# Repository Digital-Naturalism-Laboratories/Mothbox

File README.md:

# Mothbox
Developing an open source,low cost automated system for Moth-Lighting photography 

look at the wiki for up to date information on assembly and usage
https://github.com/Digital-Naturalism-Laboratories/Mothbox/wiki

It's a compact, low cost device you can get running with simple modifications of off-the-shelf parts! And no soldering really needed!

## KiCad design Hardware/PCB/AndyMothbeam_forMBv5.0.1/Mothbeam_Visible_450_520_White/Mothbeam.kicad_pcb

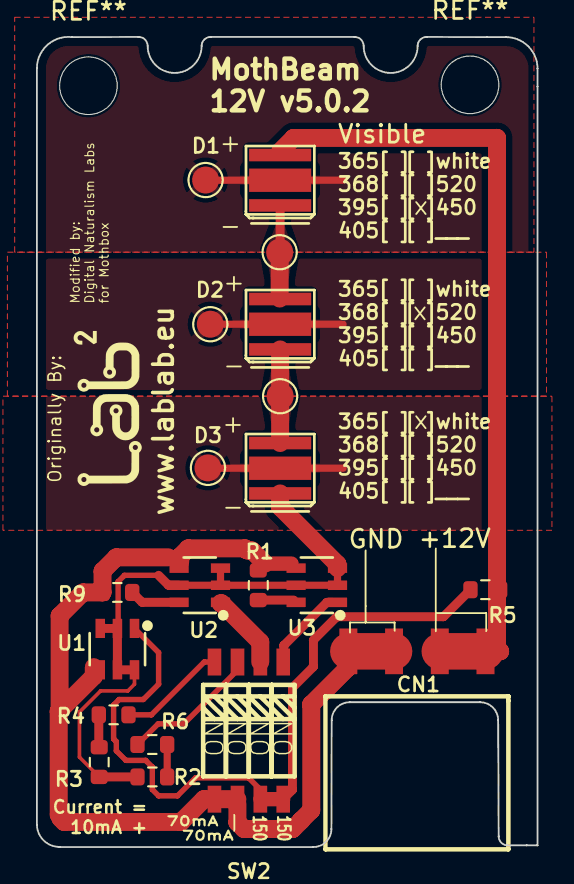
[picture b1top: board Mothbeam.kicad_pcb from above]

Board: 2 copper layers, 27.8 x 45.0 mm, 21 parts (0 on the bottom side), 17 nets.

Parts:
CN1: X6511FRS-04-C85D30; HDR-SMD_4P-P2.54-H-F
D1: LED1; LED-SMD_3P-L3.5-W3.5-R-RD-C
D2: LED2; LED-SMD_3P-L3.5-W3.5-R-RD-C
D3: LED3; LED-SMD_3P-L3.5-W3.5-R-RD-C
H1: LabLab Logo; logo_10mm_5mm
R1, R2, R3, R4, R5, R6, R9: 5.1 1/3 W; R_0603_1608Metric
SW2: SW_DIP_x04; SW-SMD_8P-L6.7-W5.4-P1.27-LS8.5
TP1, TP2, TP3, TP4, TP5: LED2+; TestPoint_Pad_D1.5mm
U1, U2, U3: BCR421U; SOT-23-6_L2.9-W1.6-P0.95-LS2.8-BL

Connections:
/LED+: CN1.3, CN1.4, D1.1 (+), R5.1
/LED-: D3.2 (-), R2.1, R3.1, U1.2 (OUT), U1.3 (OUT), U1.5 (OUT), U1.6 (REXT), U2.2 (OUT), U2.3 (OUT), U2.5 (OUT), U3.2 (OUT), U3.3 (OUT), U3.5 (OUT)
/T1: D1.3 (nc), TP2.1
/T2: D2.3, TP4.1
/T3: D3.3 (nc), TP5.1
EN: R5.2, SW2.7, SW2.8, U1.1 (EN)
GND: CN1.1, CN1.2, R1.2, R9.2, SW2.5, SW2.6, U1.4 (GND), U2.4 (GND), U3.4 (GND)
unnamed: D1.2 (-), D2.1 (A), TP3.1
unnamed: D2.2 (K), D3.1 (+), TP1.1
unnamed: R2.2, R6.1
unnamed: R3.2, R4.1
unnamed: R4.2, SW2.4
unnamed: R6.2, SW2.3
unnamed: SW2.2, U2.1 (EN)
unnamed: R9.1, U2.6 (REXT)
unnamed: SW2.1, U3.1 (EN)
unnamed: R1.1, U3.6 (REXT)

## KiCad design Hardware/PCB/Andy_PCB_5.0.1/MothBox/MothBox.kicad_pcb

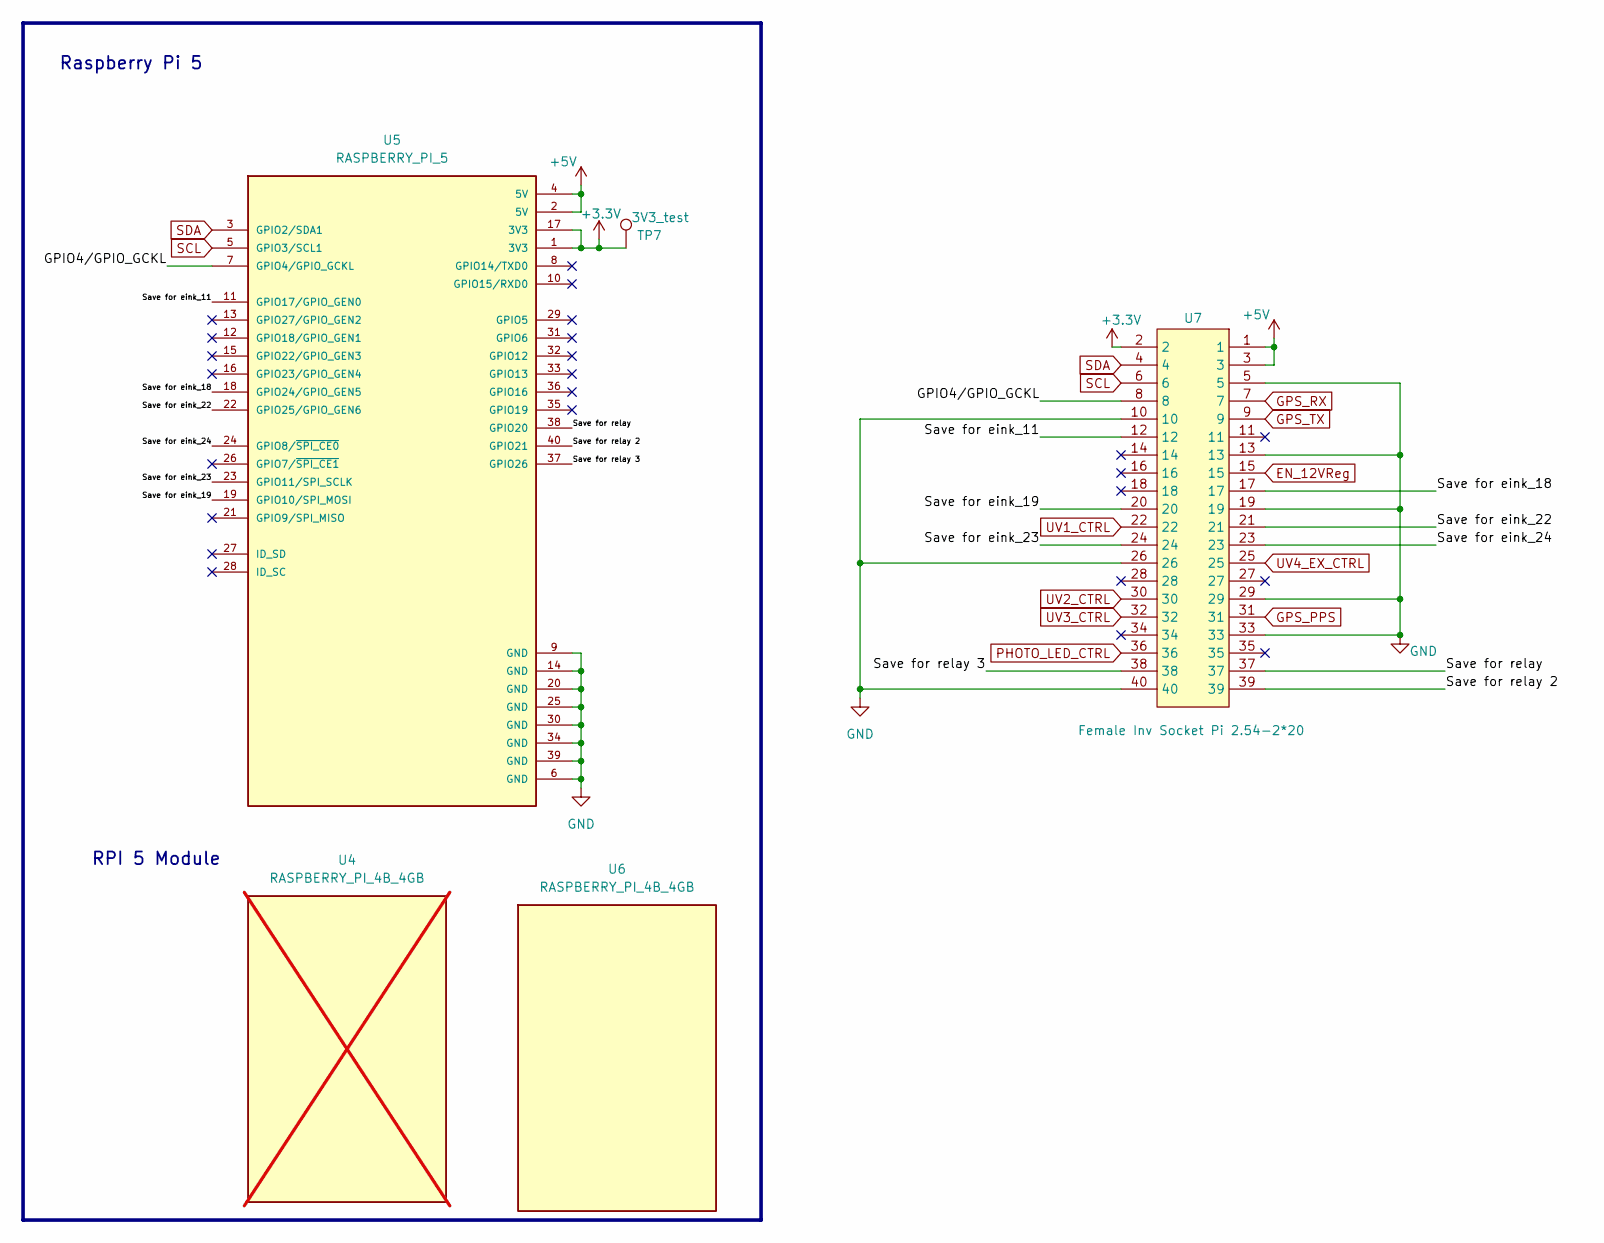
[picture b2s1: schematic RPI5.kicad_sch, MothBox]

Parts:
TP7: 3V3_test; TestPoint_THTPad_D1.0mm_Drill0.5mm
U4: RASPBERRY_PI_4B_4GB; MODULE_RASPBERRY_PI_4B_4GB; PARTREV 4; Digikey_Part_No SC1113; not fitted
U5: RASPBERRY_PI_5; EPAPER_PinHeader_2x20_P2.54mm_Vertical; LCSC_Part_No C5224014
U6: RASPBERRY_PI_4B_4GB; MODULE_RASPBERRY_PI_4B_4GB_Sideways; PARTREV 4; Digikey_Part_No SC1113
U7: Female Inv Socket Pi 2.54-2*20; HDR-TH_40P-P2.54-H-F-R2-C20-W8.5; LCSC_Part C2897440

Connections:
+3.3V: TP7.1, U5.1 (3V3), U5.17 (3V3), U7.2; also elsewhere on the board
+5V: U5.2 (5V), U5.4 (5V), U7.1, U7.3; also elsewhere on the board
/RPI5/GPIO4/GPIO_GCKL: U5.7 (GPIO4/GPIO_GCKL), U7.8
/RPI5/Save for eink_11: U5.11 (GPIO17/GPIO_GEN0), U7.12
/RPI5/Save for eink_18: U5.18 (GPIO24/GPIO_GEN5), U7.17
/RPI5/Save for eink_19: U5.19 (GPIO10/SPI_MOSI), U7.20
/RPI5/Save for eink_22: U5.22 (GPIO25/GPIO_GEN6), U7.21
/RPI5/Save for eink_23: U5.23 (GPIO11/SPI_SCLK), U7.24
/RPI5/Save for eink_24: U5.24 (GPIO8/~SPI_CE0), U7.23
/RPI5/Save for relay: U5.38 (GPIO20), U7.37
/RPI5/Save for relay 2: U5.40 (GPIO21), U7.39
/RPI5/Save for relay 3: U5.37 (GPIO26), U7.38
EN_12VReg: U7.15; also elsewhere on the board
GND: U5.6 (GND), U5.9 (GND), U5.14 (GND), U5.20 (GND), U5.25 (GND), U5.30 (GND), U5.34 (GND), U5.39 (GND), U7.5, U7.10, U7.13, U7.19, U7.26, U7.29, U7.33, U7.40; also elsewhere on the board
GPS_PPS: U7.31; also elsewhere on the board
GPS_RX: U7.7; also elsewhere on the board
GPS_TX: U7.9; also elsewhere on the board
PHOTO_LED_CTRL: U7.36; also elsewhere on the board
SCL: U5.5 (GPIO3/SCL1), U7.6; also elsewhere on the board
SDA: U5.3 (GPIO2/SDA1), U7.4; also elsewhere on the board
UV1_CTRL: U7.22; also elsewhere on the board
UV2_CTRL: U7.30; also elsewhere on the board
UV3_CTRL: U7.32; also elsewhere on the board
UV4_EX_CTRL: U7.25; also elsewhere on the board

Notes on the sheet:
RPI 5 Module
Raspberry Pi 5

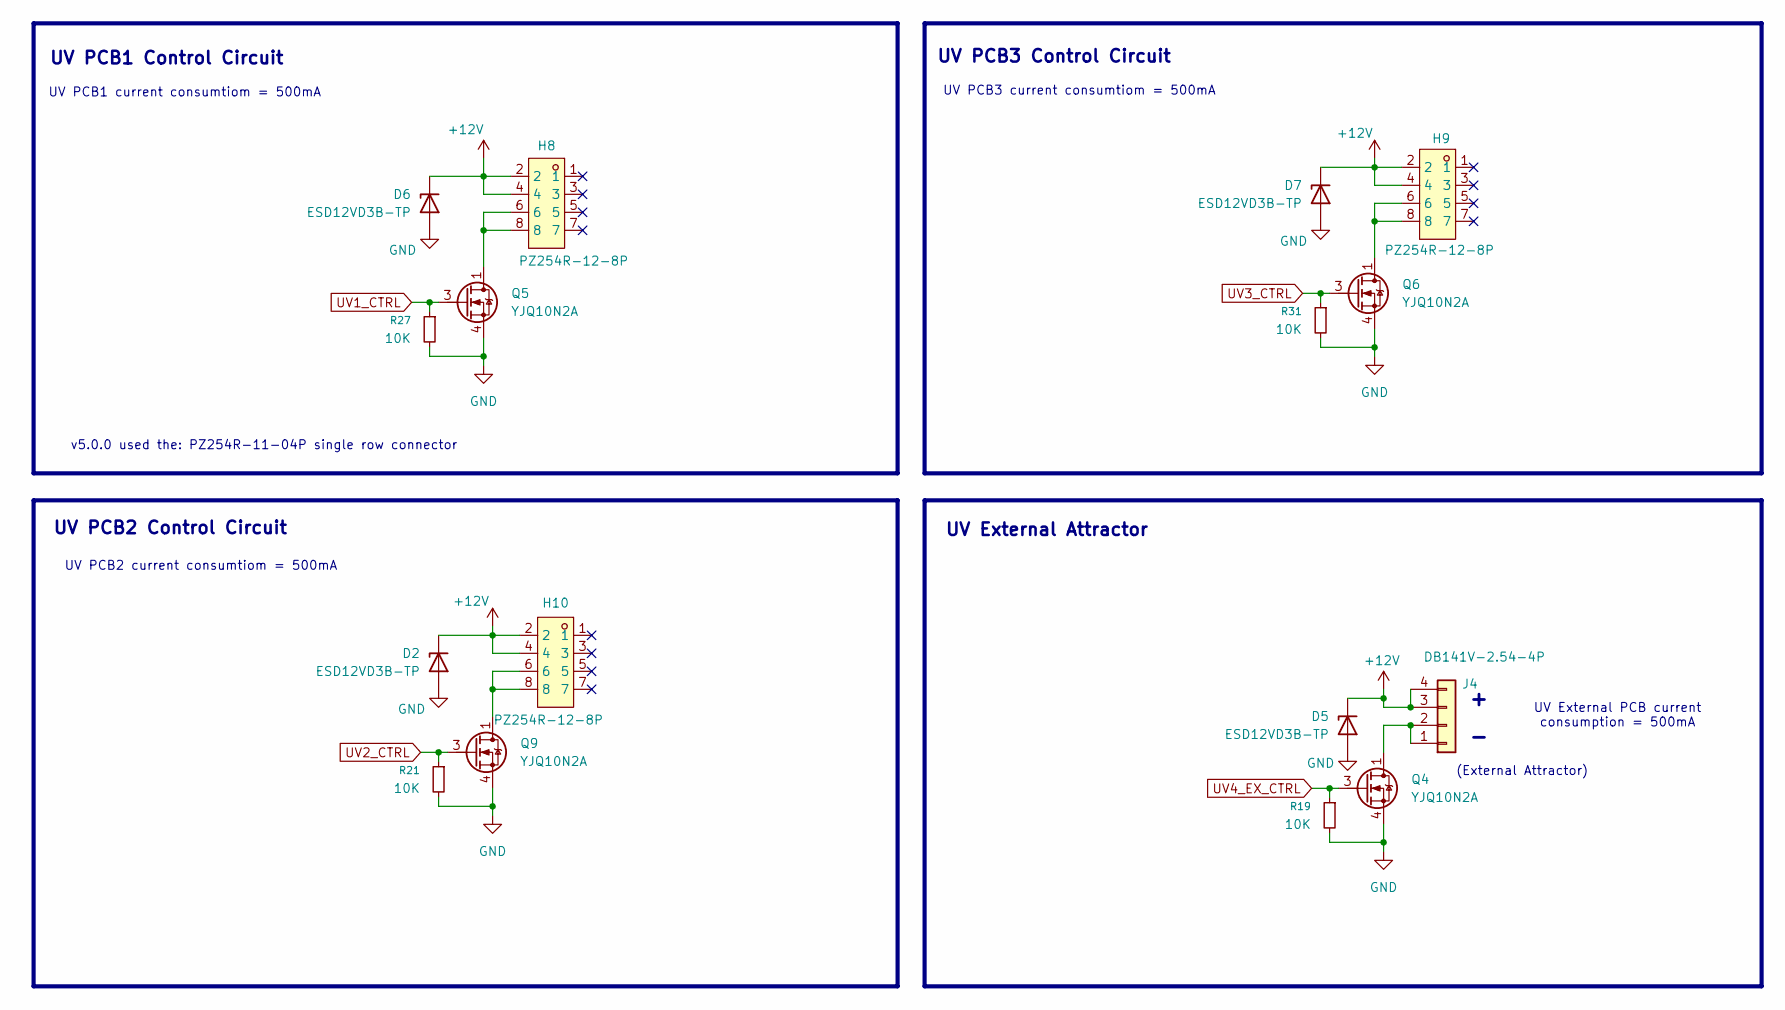
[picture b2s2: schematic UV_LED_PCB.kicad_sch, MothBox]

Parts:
D2, D5, D6, D7: ESD12VD3B-TP; D_SOD-323; LCSC_Part_No C435886
H8, H9, H10: PZ254R-12-8P; HDR-TH_8P-P2.54-H-M-R2-C4-S2.54; LCSC_Part C492432
J4: DB141V-2.54-4P; CONN-TH_4P-P2.54_DIBO_DB141V-2.54-4P; LCSC C2898746
Q4, Q5, Q6, Q9: YJQ10N2A; U-DFN2020-6_L2.0-W2.0-P0.65-BL; LCSC C919558
R19, R21, R27, R31: 10K; R_0603_1608Metric

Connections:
+12V: D2.1 (K), D5.1 (K), D6.1 (K), D7.1 (K), H8.2, H8.4, H9.2, H9.4, H10.2, H10.4, J4.3, J4.4; also elsewhere on the board
GND: D2.2 (A), D5.2 (A), D6.2 (A), D7.2 (A), Q4.4 (S), Q4.7 (S), Q5.4 (S), Q5.7 (S), Q6.4 (S), Q6.7 (S), Q9.4 (S), Q9.7 (S), R19.2, R21.2, R27.2, R31.2; also elsewhere on the board
unnamed: H8.6, H8.8, Q5.1 (D), Q5.2 (D), Q5.5 (D), Q5.6 (D), Q5.8 (D)
unnamed: H9.6, H9.8, Q6.1 (D), Q6.2 (D), Q6.5 (D), Q6.6 (D), Q6.8 (D)
unnamed: H10.6, H10.8, Q9.1 (D), Q9.2 (D), Q9.5 (D), Q9.6 (D), Q9.8 (D)
unnamed: J4.1, J4.2, Q4.1 (D), Q4.2 (D), Q4.5 (D), Q4.6 (D), Q4.8 (D)
UV1_CTRL: Q5.3 (G), R27.1; also elsewhere on the board
UV2_CTRL: Q9.3 (G), R21.1; also elsewhere on the board
UV3_CTRL: Q6.3 (G), R31.1; also elsewhere on the board
UV4_EX_CTRL: Q4.3 (G), R19.1; also elsewhere on the board

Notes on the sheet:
UV External Attractor
(External Attractor)
UV PCB1 Control Circuit
UV PCB3 Control Circuit
UV PCB1 current consumtiom = 500mA
UV PCB2 current consumtiom = 500mA
v5.0.0 used the: PZ254R-11-04P single row connector
UV PCB3 current consumtiom = 500mA
UV PCB2 Control Circuit
UV External PCB current consumption = 500mA

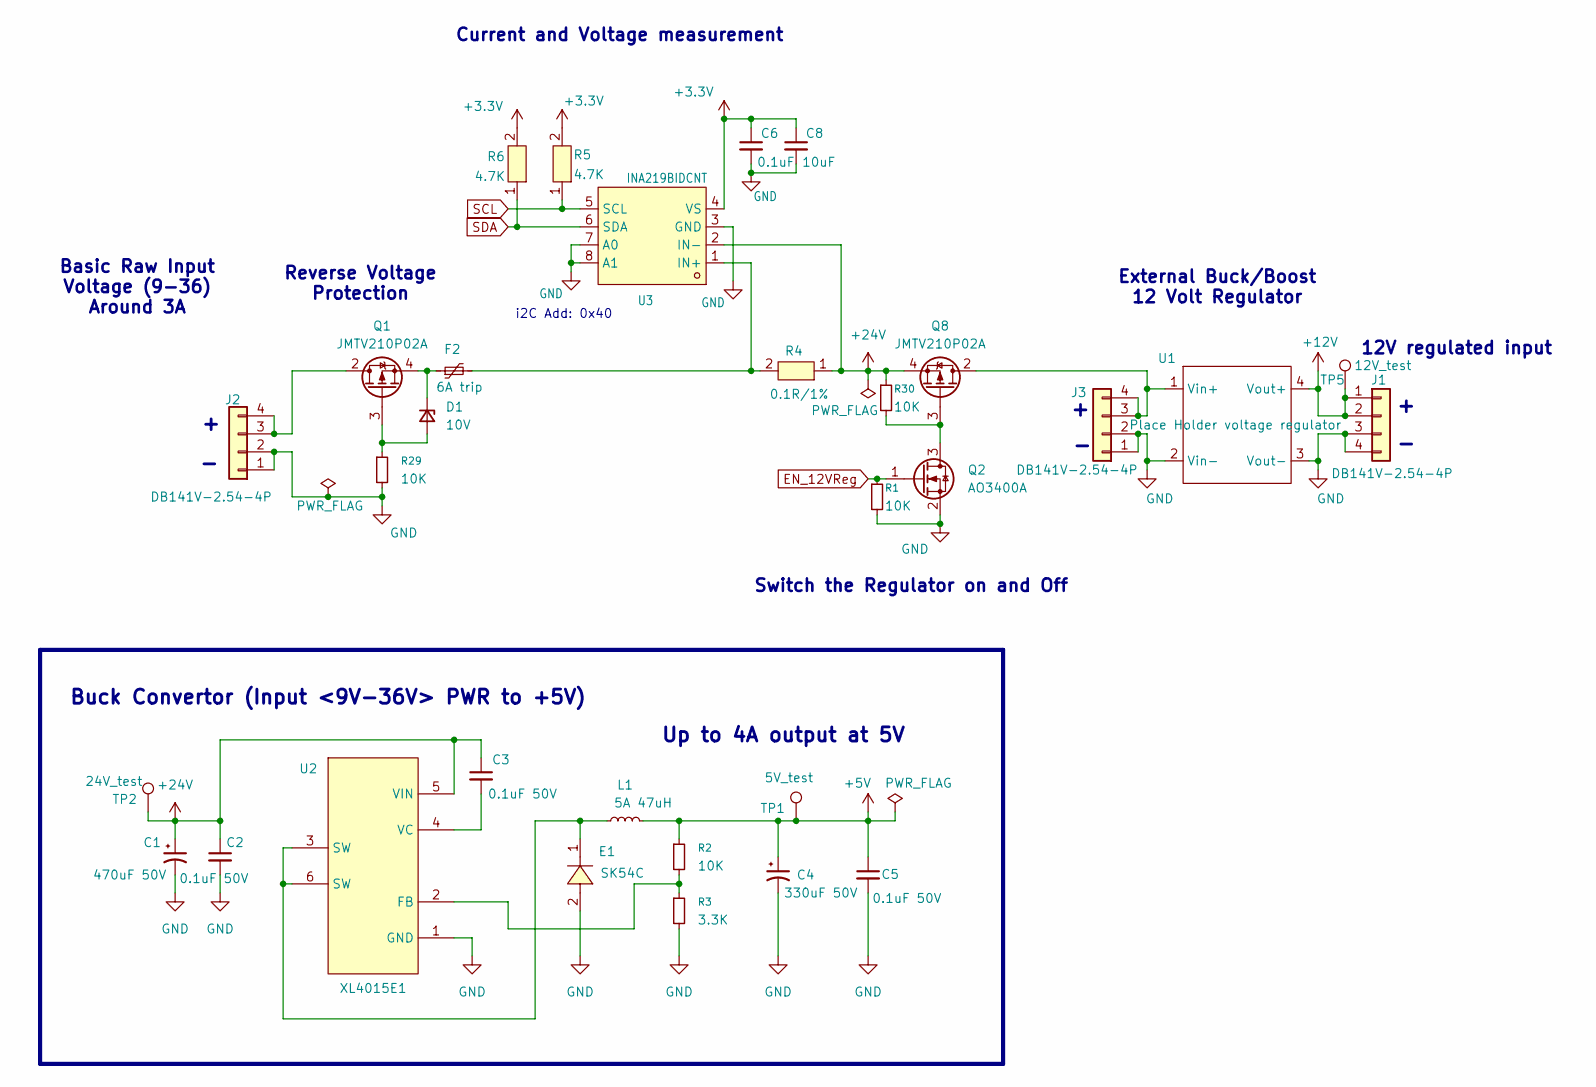
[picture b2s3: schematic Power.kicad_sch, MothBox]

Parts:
C1: 470uF 50V; CP_Elec_10x12.5; LCSC_Part_No C90272
C2, C3, C5: 0.1uF 50V; R_0603_1608Metric; LCSC_Part_No C3011704
C4: 330uF 50V; CP_Elec_10x10; LCSC_Part_No C2687701
C6: 0.1uF; C_0603_1608Metric; LCSC C14663
C8: 10uF; C_0603_1608Metric
D1: 10V; D_SOD-323; LCSC C571388
E1: SK54C; SMC_L6.9-W5.9-LS8.0-RD; PARTREV S2311; LCSC_Part C5449119
F2: 6A trip; Fuse_1812_4532Metric; LCSC C7500481
J1, J2, J3: DB141V-2.54-4P; CONN-TH_4P-P2.54_DIBO_DB141V-2.54-4P; LCSC C2898746
L1: 5A 47uH; L_Chilisin_BMRG00131360; LCSC_Part_No C497913
Q1, Q8: JMTV210P02A; U-DFN2020-6_L2.0-W2.0-P0.65-BL
Q2: AO3400A; SOT-23; LCSC C2938367
R1, R29, R30: 10K; R_0603_1608Metric
R2: 10K; R_0805_2012Metric; LCSC_Part_No C84376
R3: 3.3K; R_0805_2012Metric; LCSC_Part_No C114531
R4: 0.1R/1%; R_2512_6332Metric; LCSC_Part C23067426
R5, R6: 4.7K; R_0603_1608Metric; LCSC_Part C2930027
TP1: 5V_test; TestPoint_THTPad_D1.0mm_Drill0.5mm
TP2: 24V_test; TestPoint_THTPad_D1.0mm_Drill0.5mm
TP5: 12V_test; TestPoint_THTPad_D1.0mm_Drill0.5mm
U1: Place Holder voltage regulator
U2: XL4015E1; TO-263-5_TabPin3; PARTREV 1.5; LCSC_Part C51661
U3: INA219BIDCNT; SOT-23-8; LCSC_Part C87469

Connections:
+3.3V: C6.1, C8.1, R5.2, R6.2, U3.4 (VS); also elsewhere on the board
+5V: C4.1, C5.1, L1.2, R2.1, TP1.1; also elsewhere on the board
+12V: J1.1, J1.2, TP5.1, U1.4 (Vout+); also elsewhere on the board
+24V: C1.1, C2.1, C3.1, Q8.4 (S), Q8.7 (S), R4.1, R30.1, TP2.1, U2.5 (VIN), U3.2 (IN-)
EN_12VReg: Q2.1 (G), R1.1; also elsewhere on the board
GND: C1.2, C2.2, C4.2, C5.2, C6.2, C8.2, E1.2 (A), J1.3, J1.4, J2.1, J2.2, J3.1, J3.2, Q2.2 (S), R1.2, R3.2, R29.2, U1.2 (Vin-), U1.3 (Vout-), U2.1 (GND), U3.3 (GND), U3.7 (A0), U3.8 (A1); also elsewhere on the board
unnamed: D1.2 (A), Q1.3 (G), R29.1
unnamed: D1.1 (K), F2.1, Q1.4 (S), Q1.7 (S)
unnamed: E1.1 (C), L1.1, U2.3 (SW), U2.6 (SW)
unnamed: J2.3, J2.4, Q1.1 (D), Q1.2 (D), Q1.5 (D), Q1.6 (D), Q1.8 (D)
unnamed: J3.3, J3.4, Q8.1 (D), Q8.2 (D), Q8.5 (D), Q8.6 (D), Q8.8 (D), U1.1 (Vin+)
unnamed: Q2.3 (D), Q8.3 (G), R30.2
unnamed: R2.2, R3.1, U2.2 (FB)
unnamed: C3.2, U2.4 (VC)
unnamed: F2.2, R4.2, U3.1 (IN+)
SCL: R5.1, U3.5 (SCL); also elsewhere on the board
SDA: R6.1, U3.6 (SDA); also elsewhere on the board

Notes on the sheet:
Current and Voltage measurement
i2C Add: 0x40
Buck Convertor (Input <9V-36V> PWR to +5V)
Reverse Voltage Protection
12V regulated input
Switch the Regulator on and Off
Up to 4A output at 5V
Basic Raw Input Voltage (9-36) Around 3A
External Buck/Boost 12 Volt Regulator

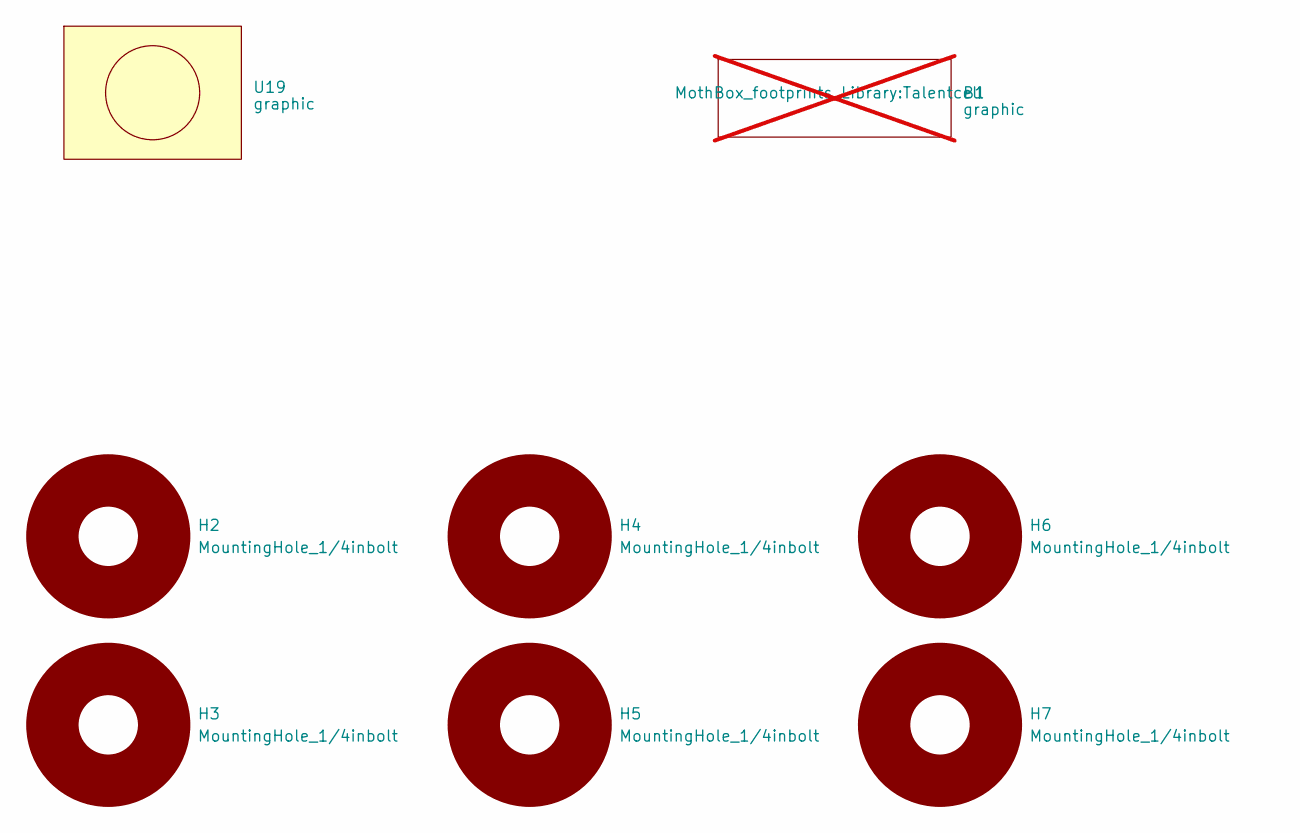
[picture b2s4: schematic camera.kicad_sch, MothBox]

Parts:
B1: graphic; Talentcell; not fitted
H2, H3, H4, H5, H6, H7: MountingHole_1/4inbolt; MountingHole_6.4mm_M6_Pad
U19: graphic; Arducam Owlsight

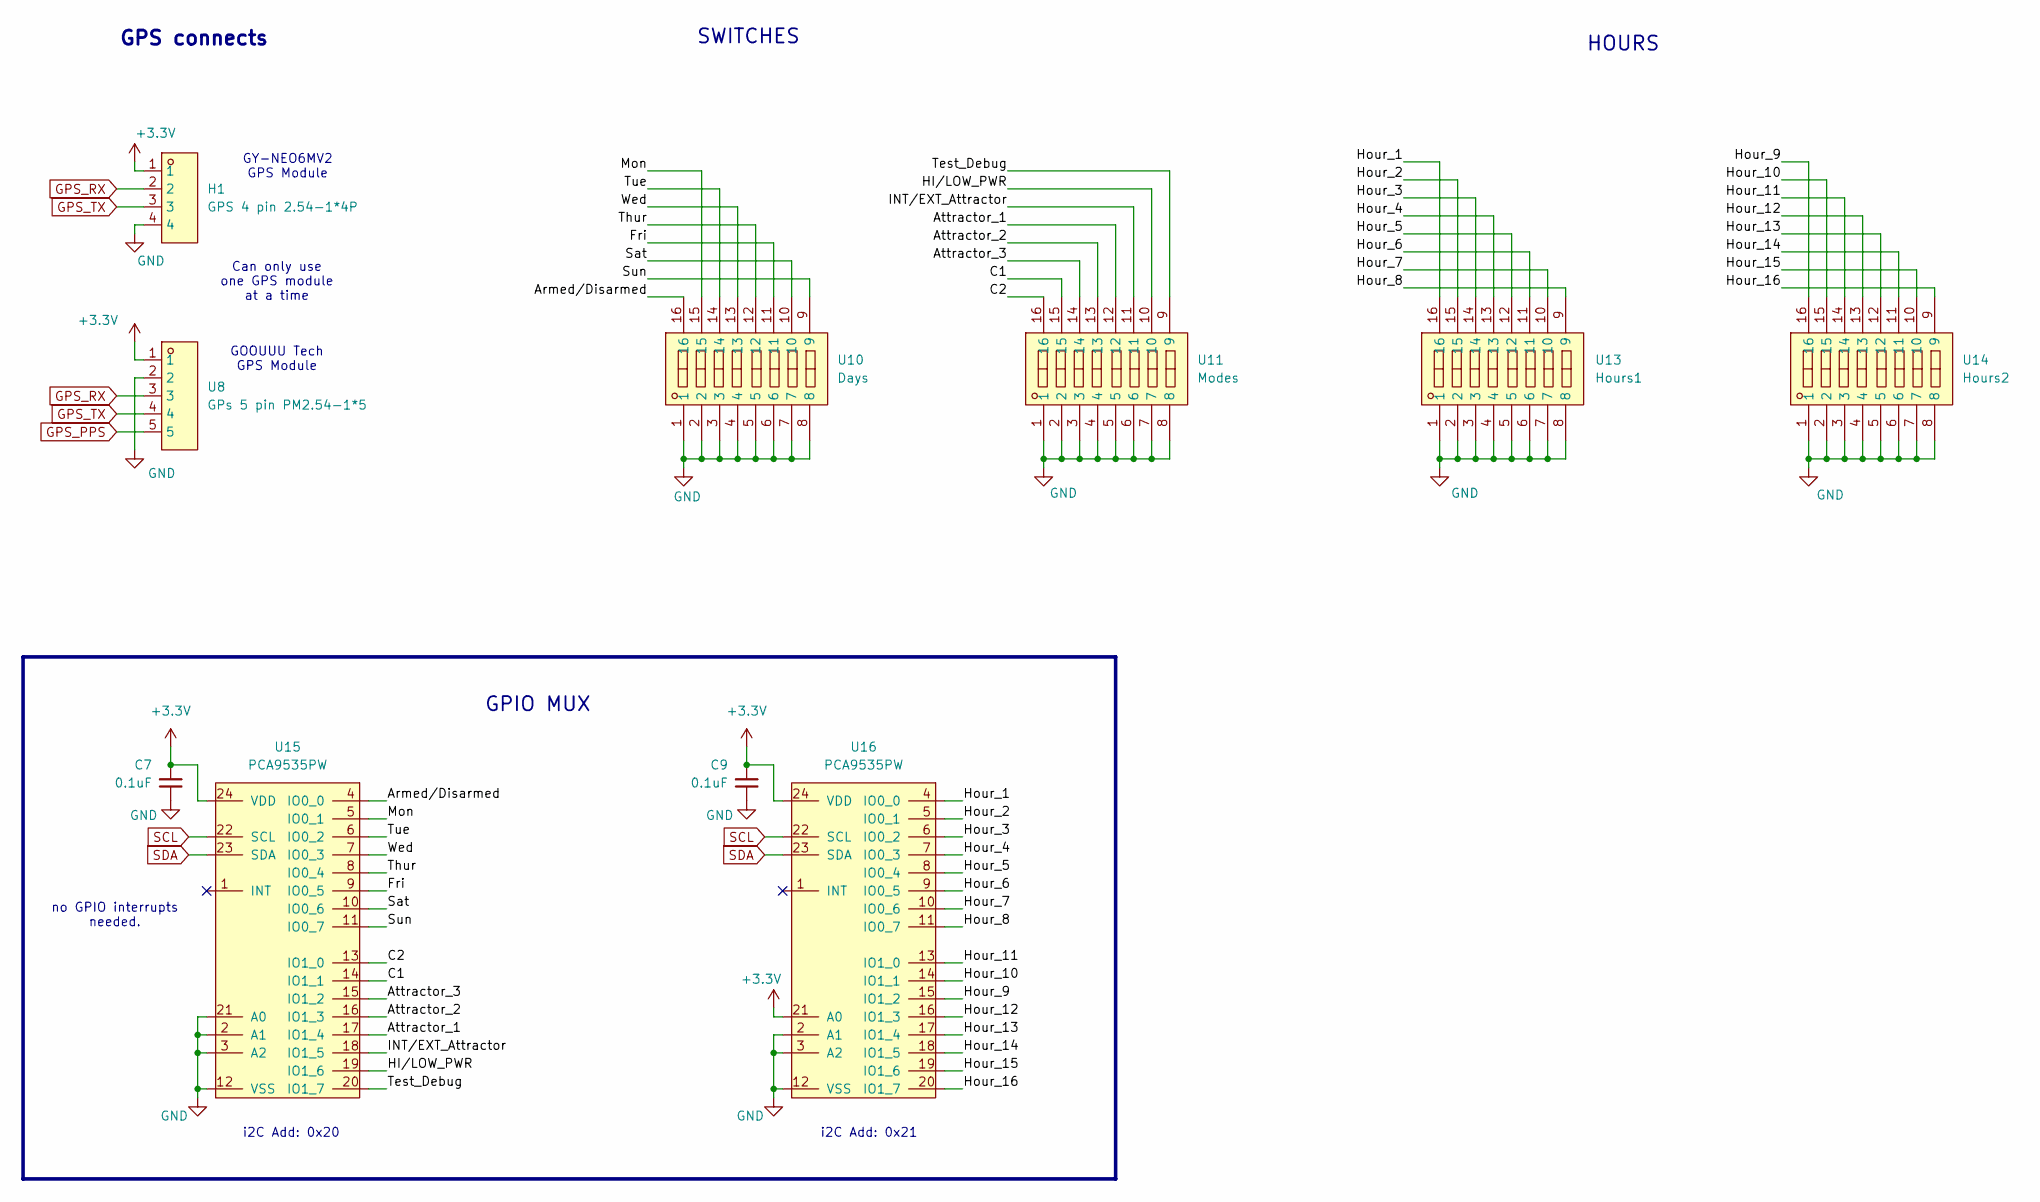
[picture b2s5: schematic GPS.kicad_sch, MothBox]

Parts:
C7, C9: 0.1uF; C_0603_1608Metric; Digikey_Part_No 311-1140-2-ND
H1: GPS 4 pin 2.54-1*4P; PinSocket_1x04_P2.54mm_Vertical; LCSC_Part C2718488
U8: GPs 5 pin PM2.54-1*5; PinSocket_1x05_P2.54mm_Vertical; LCSC_Part C5116488
U10: Days; SW-SMD_SMXS-08K-TP; LCSC_Part C5439767
U11: Modes; SW-SMD_SMXS-08K-TP; LCSC_Part C5439767
U13: Hours1; SW-SMD_SMXS-08K-TP; LCSC_Part C5439767
U14: Hours2; SW-SMD_SMXS-08K-TP; LCSC_Part C5439767
U15: PCA9535PW; TSSOP-24_4.4x7.8mm_P0.65mm
U16: PCA9535PW; TSSOP-24_4.4x7.8mm_P0.65mm; LCSC C42420616

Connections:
+3.3V: C7.2, C9.2, H1.1, U8.1, U15.24 (VDD), U16.21 (A0), U16.24 (VDD); also elsewhere on the board
/GPS and Switches/Armed/Disarmed: U10.16, U15.4 (IO0_0)
/GPS and Switches/Attractor_1: U11.12, U15.17 (IO1_4)
/GPS and Switches/Attractor_2: U11.13, U15.16 (IO1_3)
/GPS and Switches/Attractor_3: U11.14, U15.15 (IO1_2)
/GPS and Switches/C1: U11.15, U15.14 (IO1_1)
/GPS and Switches/C2: U11.16, U15.13 (IO1_0)
/GPS and Switches/Fri: U10.11, U15.9 (IO0_5)
/GPS and Switches/HI/LOW_PWR: U11.10, U15.19 (IO1_6)
/GPS and Switches/Hour_1: U13.16, U16.4 (IO0_0)
/GPS and Switches/Hour_2: U13.15, U16.5 (IO0_1)
/GPS and Switches/Hour_3: U13.14, U16.6 (IO0_2)
/GPS and Switches/Hour_4: U13.13, U16.7 (IO0_3)
/GPS and Switches/Hour_5: U13.12, U16.8 (IO0_4)
/GPS and Switches/Hour_6: U13.11, U16.9 (IO0_5)
/GPS and Switches/Hour_7: U13.10, U16.10 (IO0_6)
/GPS and Switches/Hour_8: U13.9, U16.11 (IO0_7)
/GPS and Switches/Hour_9: U14.16, U16.15 (IO1_2)
/GPS and Switches/Hour_10: U14.15, U16.14 (IO1_1)
/GPS and Switches/Hour_11: U14.14, U16.13 (IO1_0)
/GPS and Switches/Hour_12: U14.13, U16.16 (IO1_3)
/GPS and Switches/Hour_13: U14.12, U16.17 (IO1_4)
/GPS and Switches/Hour_14: U14.11, U16.18 (IO1_5)
/GPS and Switches/Hour_15: U14.10, U16.19 (IO1_6)
/GPS and Switches/Hour_16: U14.9, U16.20 (IO1_7)
/GPS and Switches/INT/EXT_Attractor: U11.11, U15.18 (IO1_5)
/GPS and Switches/Mon: U10.15, U15.5 (IO0_1)
/GPS and Switches/Sat: U10.10, U15.10 (IO0_6)
/GPS and Switches/Sun: U10.9, U15.11 (IO0_7)
/GPS and Switches/Test_Debug: U11.9, U15.20 (IO1_7)
/GPS and Switches/Thur: U10.12, U15.8 (IO0_4)
/GPS and Switches/Tue: U10.14, U15.6 (IO0_2)
/GPS and Switches/Wed: U10.13, U15.7 (IO0_3)
GND: C7.1, C9.1, H1.4, U8.2, U10.1, U10.2, U10.3, U10.4, U10.5, U10.6, U10.7, U10.8, U11.1, U11.2, U11.3, U11.4, U11.5, U11.6, U11.7, U11.8, U13.1, U13.2, U13.3, U13.4, U13.5, U13.6, U13.7, U13.8, U14.1, U14.2, U14.3, U14.4, U14.5, U14.6, U14.7, U14.8, U15.2 (A1), U15.3 (A2), U15.12 (VSS), U15.21 (A0), U16.2 (A1), U16.3 (A2), U16.12 (VSS); also elsewhere on the board
GPS_PPS: U8.5; also elsewhere on the board
GPS_RX: H1.2, U8.3; also elsewhere on the board
GPS_TX: H1.3, U8.4; also elsewhere on the board
SCL: U15.22 (SCL), U16.22 (SCL); also elsewhere on the board
SDA: U15.23 (SDA), U16.23 (SDA); also elsewhere on the board

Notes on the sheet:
Can only use one GPS module at a time
no GPIO interrupts needed.
GY-NEO6MV2 GPS Module
GPS connects
HOURS
GOOUUU Tech GPS Module
i2C Add: 0x20
i2C Add: 0x21
GPIO MUX
SWITCHES

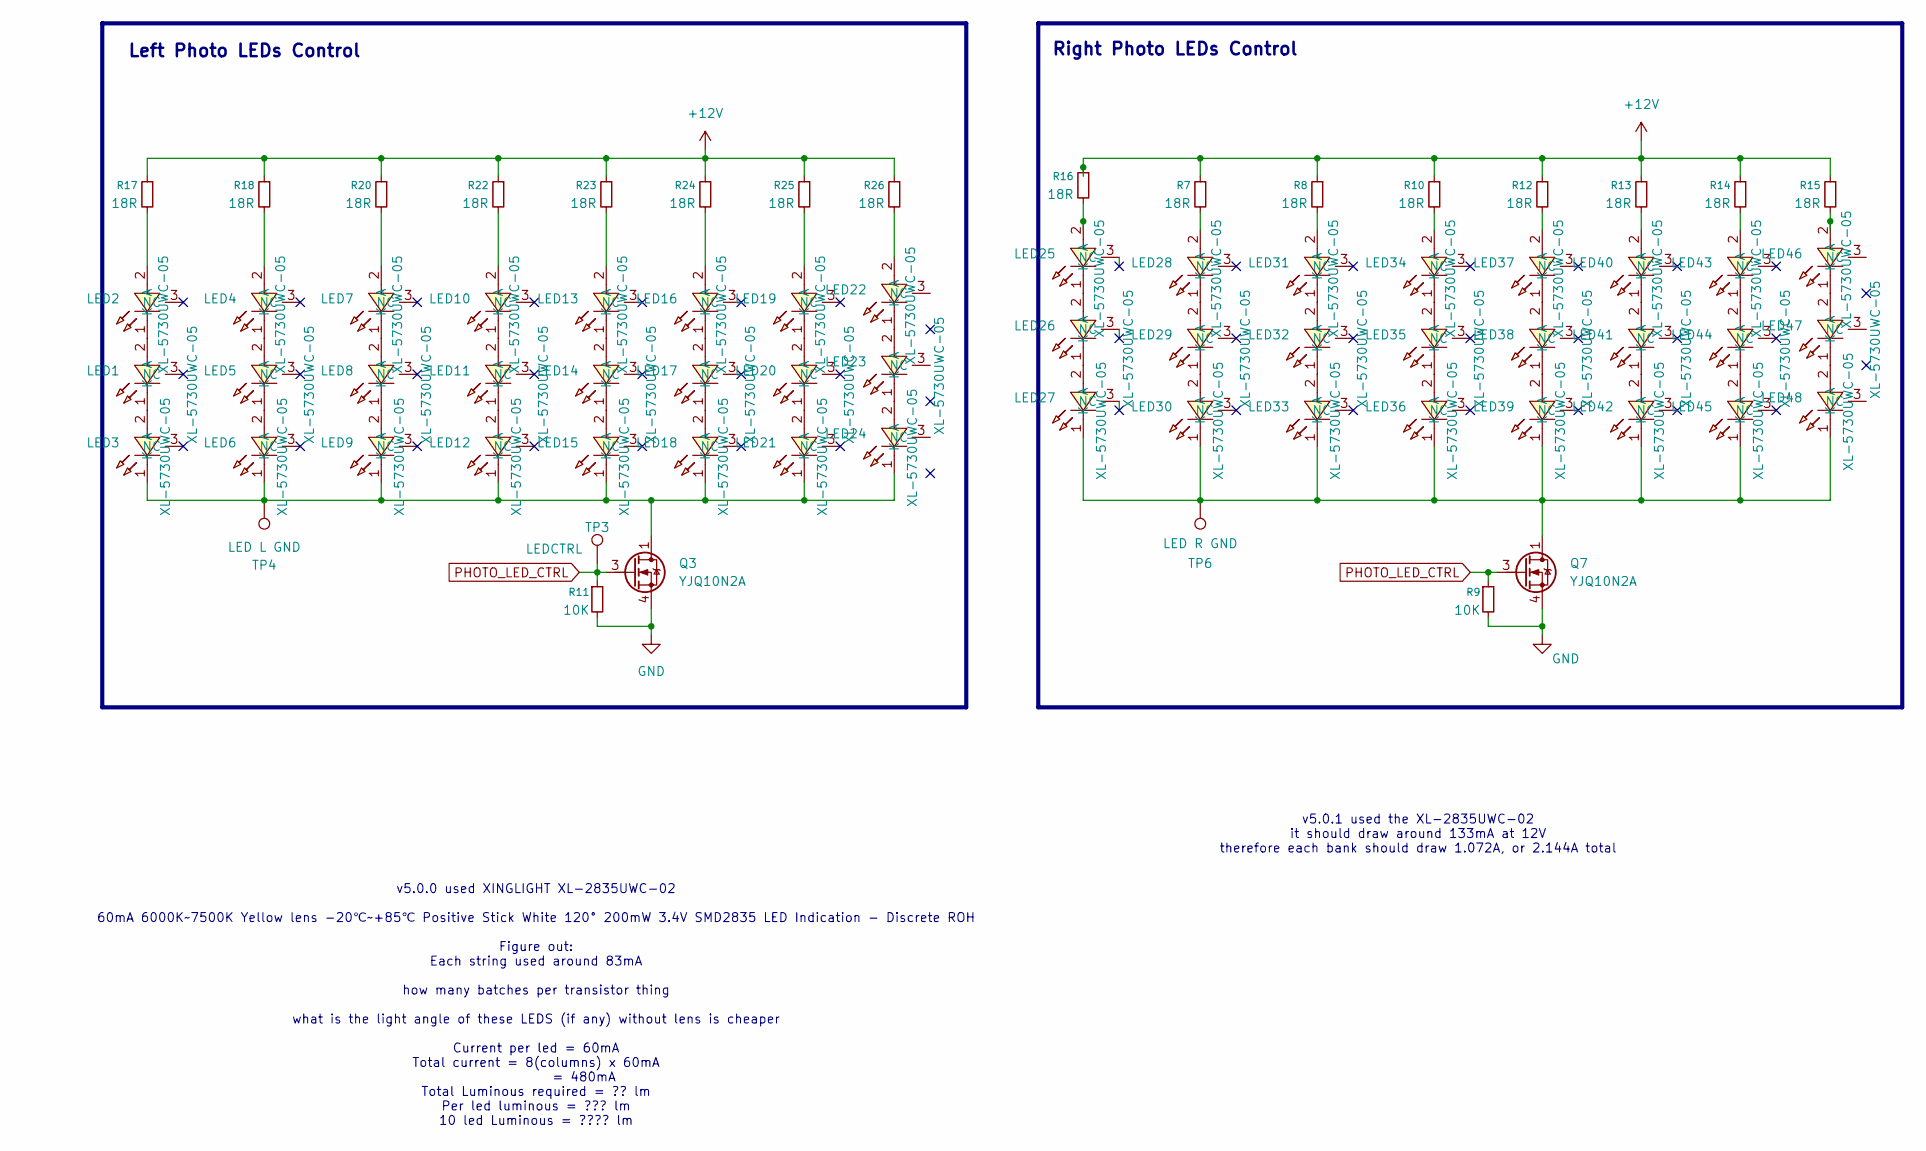
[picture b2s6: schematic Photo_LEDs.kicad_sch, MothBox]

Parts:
LED1, LED2, LED3, LED4, LED5, LED6, LED7, LED8, LED9, LED10, LED11, LED12, LED13, LED14, LED15, LED16, LED17, LED18, LED19, LED20, LED21, LED22, LED23, LED24, LED25, LED26, LED27, LED28, LED29, LED30, LED31, LED32, LED33, LED34, LED35, LED36, LED37, LED38, LED39, LED40, LED41, LED42, LED43, LED44, LED45, LED46, LED47, LED48: XL-5730UWC-05; LED-SMD_3P-L5.7-W3.0-RD; LCSC_Part C2843887
Q3, Q7: YJQ10N2A; U-DFN2020-6_L2.0-W2.0-P0.65-BL; LCSC C919558
R7, R8, R10, R12, R13, R14, R15, R16, R17, R18, R20, R22, R23, R24, R25, R26: 18R; R_1210_3225Metric; LCSC C48392080
R9, R11: 10K; R_0603_1608Metric
TP3: LEDCTRL; TestPoint_THTPad_D1.0mm_Drill0.5mm
TP4: LED L GND; TestPoint_THTPad_D1.0mm_Drill0.5mm
TP6: LED R GND; TestPoint_THTPad_D1.0mm_Drill0.5mm

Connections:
+12V: R7.1, R8.1, R10.1, R12.1, R13.1, R14.1, R15.1, R16.1, R17.1, R18.1, R20.1, R22.1, R23.1, R24.1, R25.1, R26.1; also elsewhere on the board
GND: Q3.4 (S), Q3.7 (S), Q7.4 (S), Q7.7 (S), R9.2, R11.2; also elsewhere on the board
unnamed: LED1.2 (A), LED2.1 (K)
unnamed: LED1.1 (K), LED3.2 (A)
unnamed: LED2.2 (A), R17.2
unnamed: LED4.2 (A), R18.2
unnamed: LED4.1 (K), LED5.2 (A)
unnamed: LED5.1 (K), LED6.2 (A)
unnamed: LED7.2 (A), R20.2
unnamed: LED7.1 (K), LED8.2 (A)
unnamed: LED8.1 (K), LED9.2 (A)
unnamed: LED10.2 (A), R22.2
unnamed: LED10.1 (K), LED11.2 (A)
unnamed: LED11.1 (K), LED12.2 (A)
unnamed: LED3.1 (K), LED6.1 (K), LED9.1 (K), LED12.1 (K), LED15.1 (K), LED18.1 (K), LED21.1 (K), LED24.1 (K), Q3.1 (D), Q3.2 (D), Q3.5 (D), Q3.6 (D), Q3.8 (D), TP4.1
unnamed: LED13.2 (A), R23.2
unnamed: LED13.1 (K), LED14.2 (A)
unnamed: LED14.1 (K), LED15.2 (A)
unnamed: LED16.2 (A), R24.2
unnamed: LED16.1 (K), LED17.2 (A)
unnamed: LED17.1 (K), LED18.2 (A)
unnamed: LED19.2 (A), R25.2
unnamed: LED19.1 (K), LED20.2 (A)
unnamed: LED20.1 (K), LED21.2 (A)
unnamed: LED22.2 (A), R26.2
unnamed: LED22.1 (K), LED23.2 (A)
unnamed: LED23.1 (K), LED24.2 (A)
unnamed: LED25.2 (A), R16.2
unnamed: LED25.1 (K), LED26.2 (A)
unnamed: LED26.1 (K), LED27.2 (A)
unnamed: LED27.1 (K), LED30.1 (K), LED33.1 (K), LED36.1 (K), LED39.1 (K), LED42.1 (K), LED45.1 (K), LED48.1 (K), Q7.1 (D), Q7.2 (D), Q7.5 (D), Q7.6 (D), Q7.8 (D), TP6.1
unnamed: LED28.2 (A), R7.2
unnamed: LED28.1 (K), LED29.2 (A)
unnamed: LED29.1 (K), LED30.2 (A)
unnamed: LED31.2 (A), R8.2
unnamed: LED31.1 (K), LED32.2 (A)
unnamed: LED32.1 (K), LED33.2 (A)
unnamed: LED34.2 (A), R10.2
unnamed: LED34.1 (K), LED35.2 (A)
unnamed: LED35.1 (K), LED36.2 (A)
unnamed: LED37.2 (A), R12.2
unnamed: LED37.1 (K), LED38.2 (A)
unnamed: LED38.1 (K), LED39.2 (A)
unnamed: LED40.2 (A), R13.2
unnamed: LED40.1 (K), LED41.2 (A)
unnamed: LED41.1 (K), LED42.2 (A)
unnamed: LED43.2 (A), R14.2
unnamed: LED43.1 (K), LED44.2 (A)
unnamed: LED44.1 (K), LED45.2 (A)
unnamed: LED46.2 (A), R15.2
unnamed: LED46.1 (K), LED47.2 (A)
unnamed: LED47.1 (K), LED48.2 (A)
PHOTO_LED_CTRL: Q3.3 (G), Q7.3 (G), R9.1, R11.1, TP3.1; also elsewhere on the board

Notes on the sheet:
v5.0.0 used XINGLIGHT XL-2835UWC-02 60mA 6000K~7500K Yellow lens -20℃~+85℃ Positive Stick White 120° 200mW 3.4V SMD2835 LED Indication - Discrete ROH Figure out: Each string used around 83mA how many batches per transistor thing what is the light angle of these LEDS (if any) without lens is cheaper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
Right Photo LEDs Control
Left Photo LEDs Control
v5.0.1 used the XL-2835UWC-02 it should draw around 133mA at 12V therefore each bank should draw 1.072A, or 2.144A total

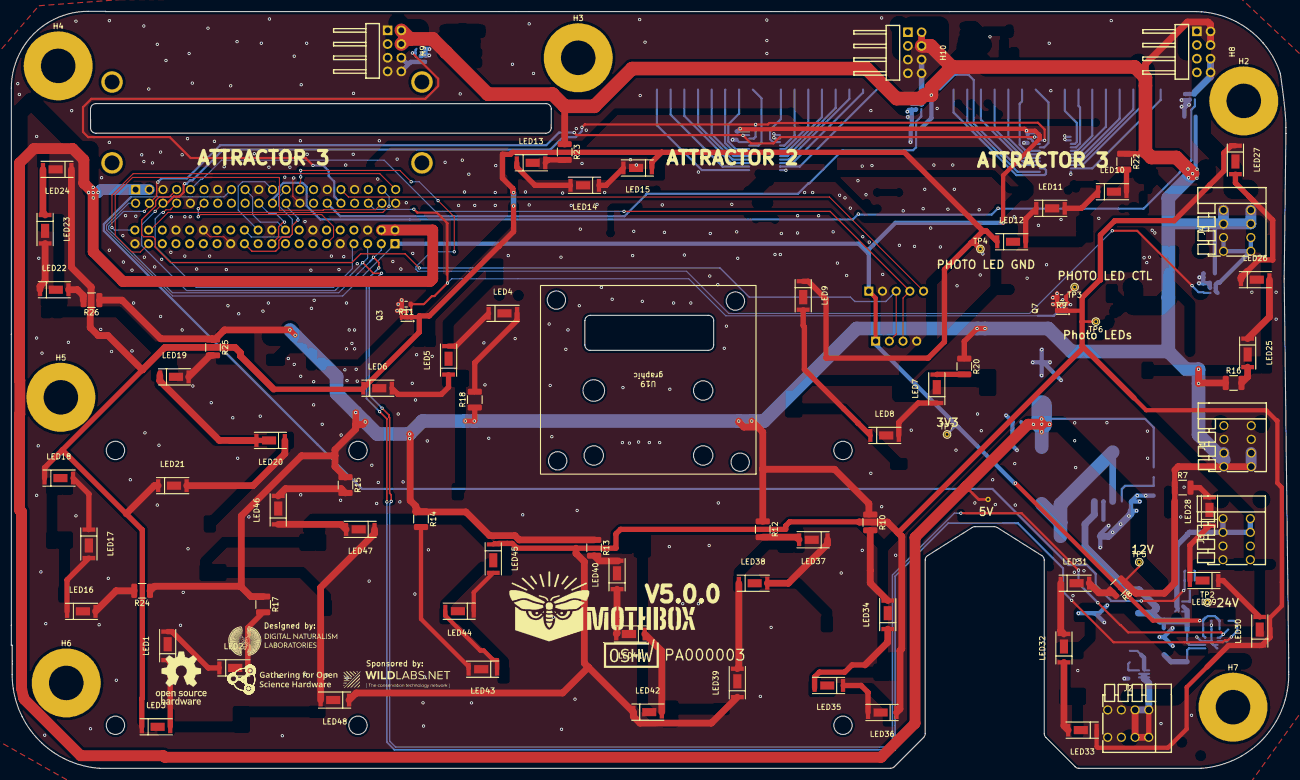
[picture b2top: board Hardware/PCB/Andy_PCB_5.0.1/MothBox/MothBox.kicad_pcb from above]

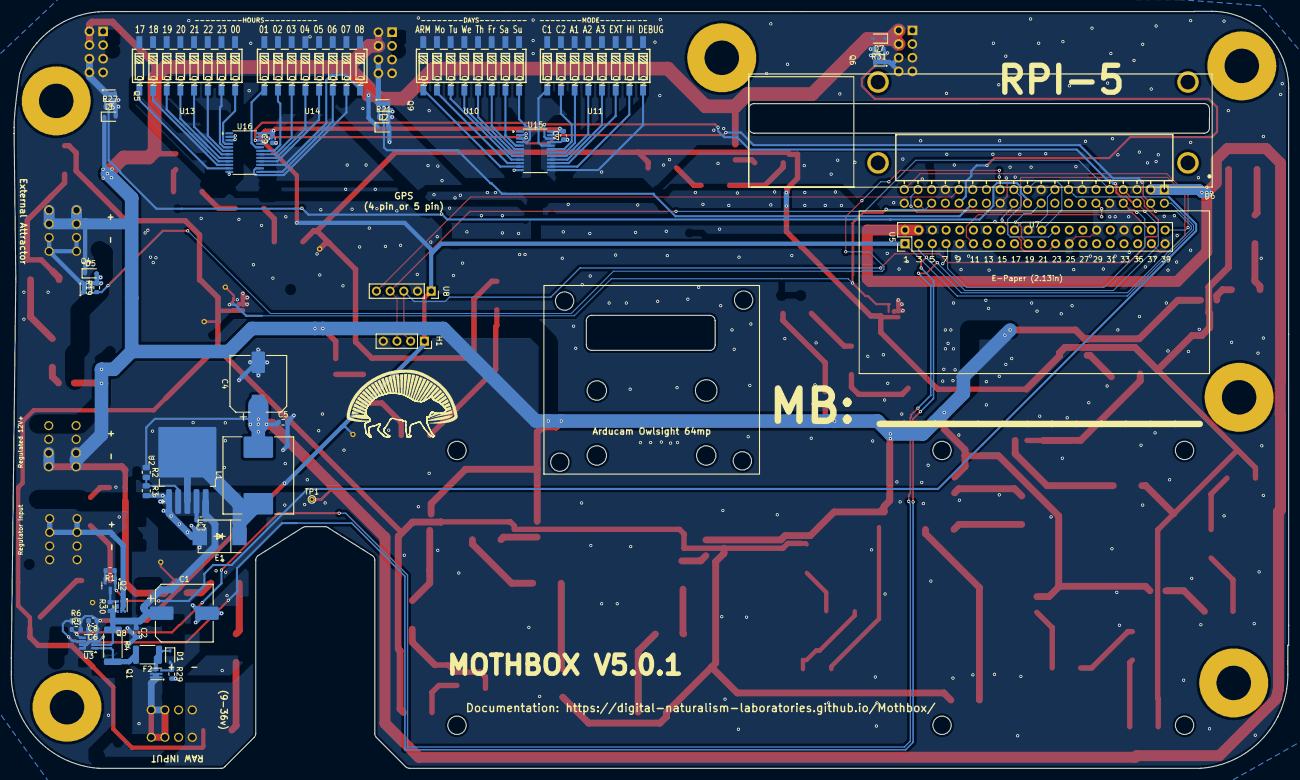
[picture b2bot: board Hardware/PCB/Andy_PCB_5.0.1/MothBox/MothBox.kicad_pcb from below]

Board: 2 copper layers, 237.0 x 140.5 mm, 139 parts (51 on the bottom side), 121 nets.
